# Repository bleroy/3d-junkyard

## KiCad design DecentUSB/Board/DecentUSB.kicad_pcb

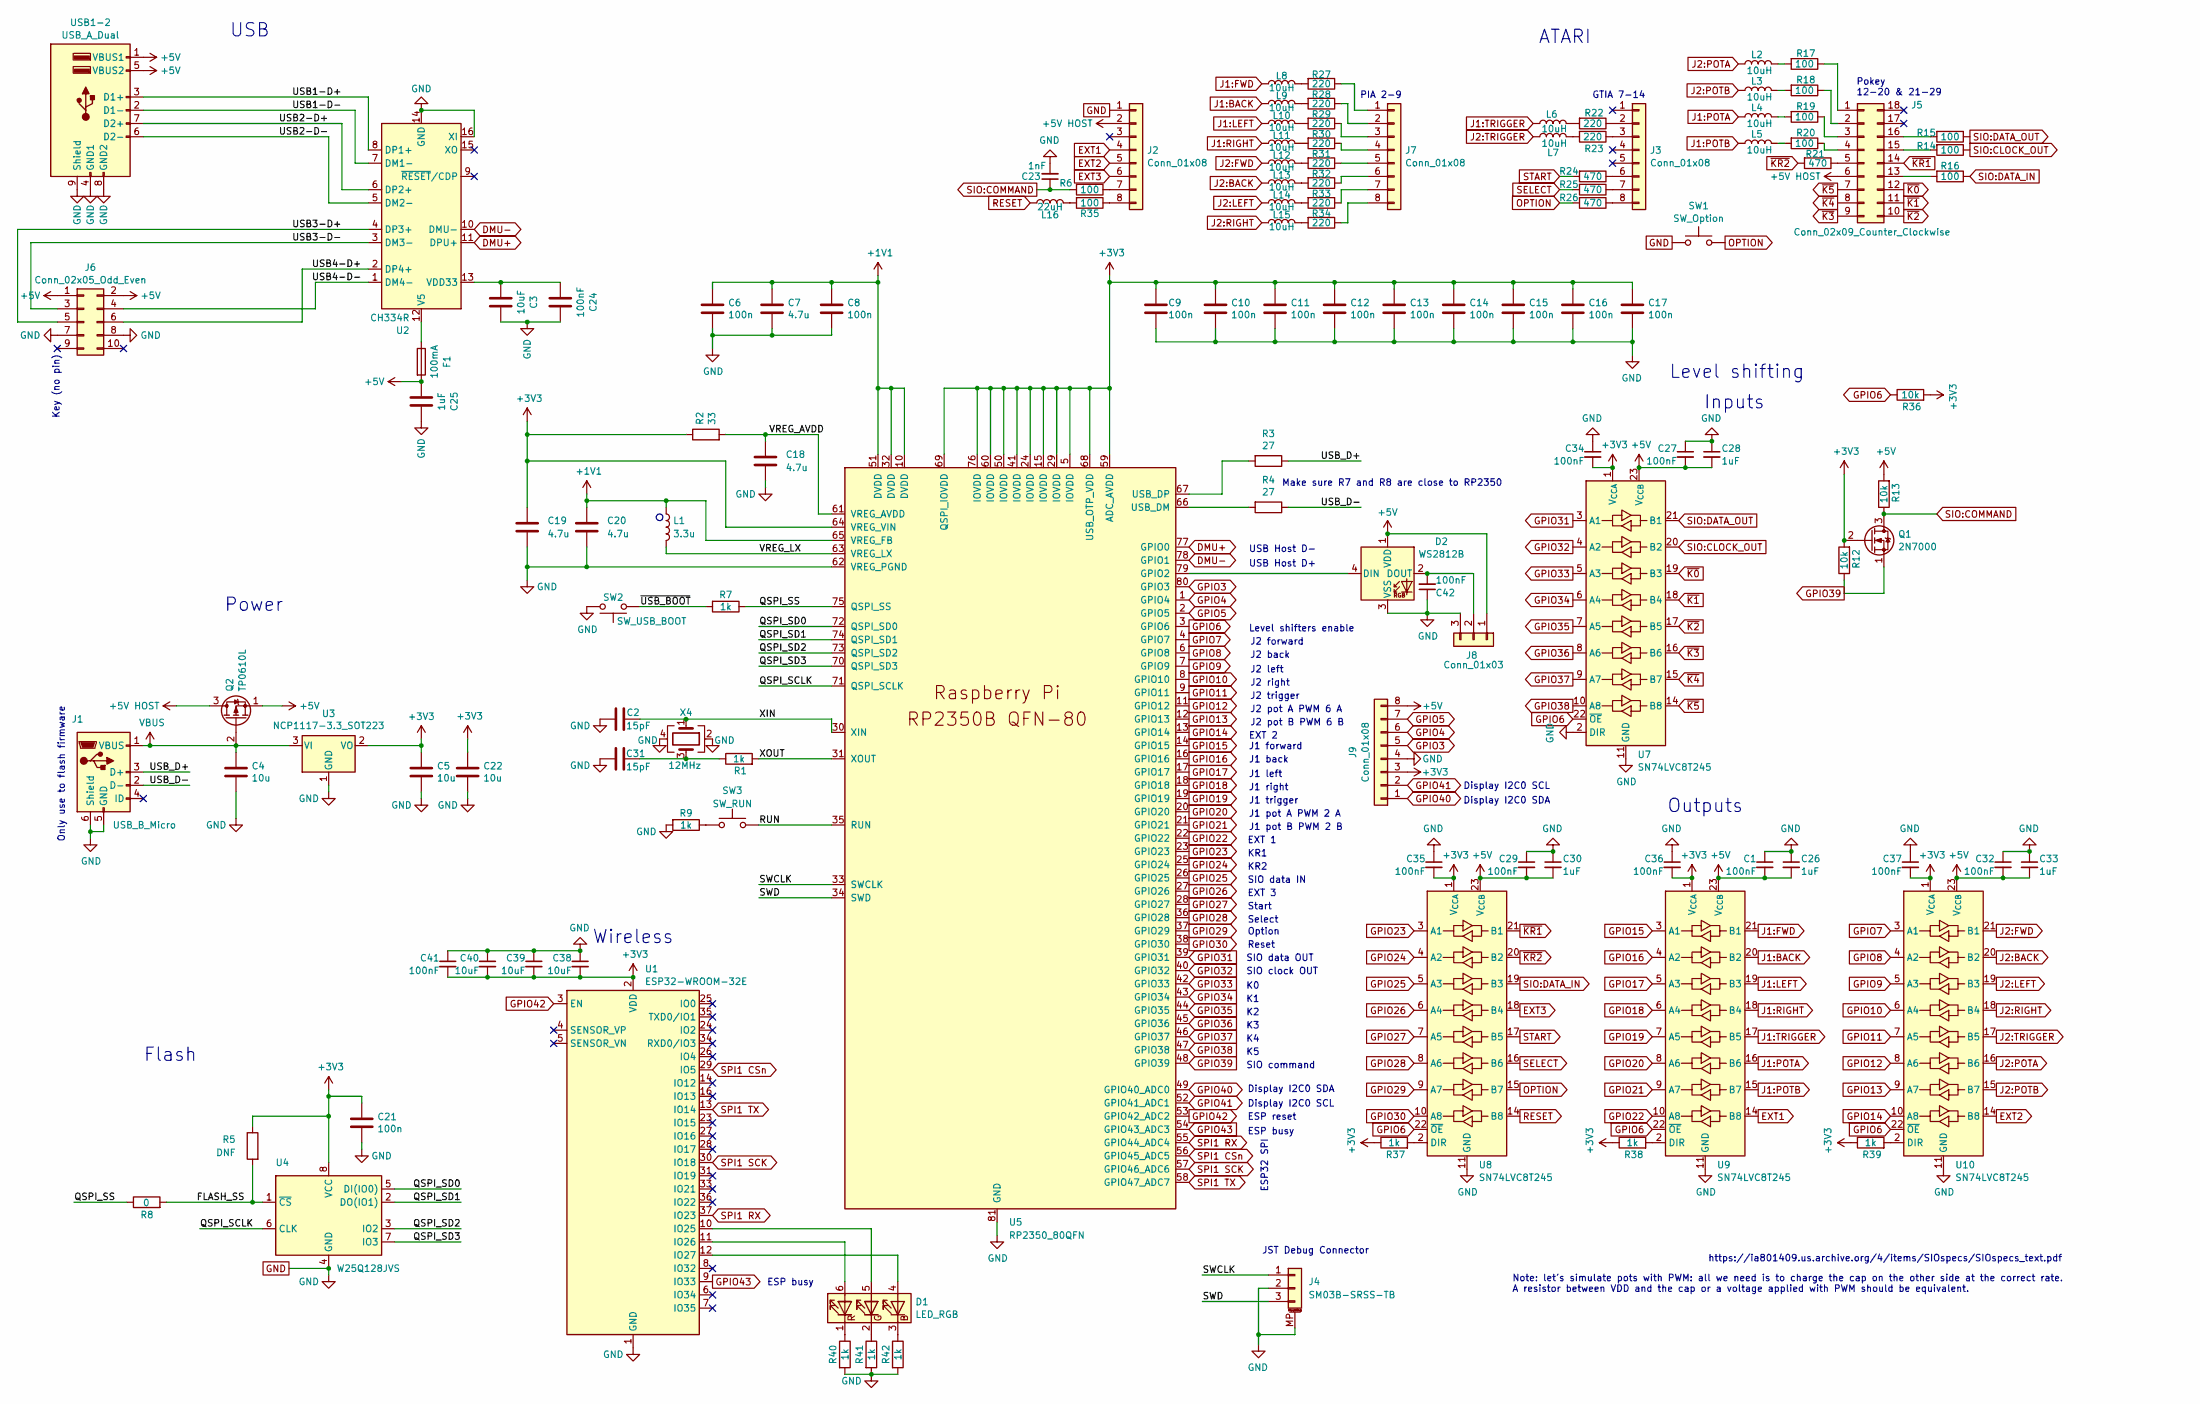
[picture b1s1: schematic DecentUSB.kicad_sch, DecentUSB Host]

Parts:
C1, C27, C29, C32, C34, C35, C36, C37, C41, C42: 100nF; C_0402_1005Metric
C2, C31: 15pF; C_0402_1005Metric
C3: 10uF; C_0402_1005Metric; JLCPCB Part # C19702
C4, C5, C22: 10u; C_0402_1005Metric
C6, C8, C9, C10, C11, C12, C13, C14, C15, C16, C17, C21: 100n; C_0402_1005Metric
C7, C18, C19, C20: 4.7u; C_0402_1005Metric
C23: 1nF; C_0402_1005Metric
C24: 100nF; C_0402_1005Metric; JLCPCB Part # C14663
C25: 1uF; C_0402_1005Metric; JLCPCB Part # C15849
C26, C28, C30, C33: 1uF; C_0402_1005Metric
C38, C39, C40: 10uF; C_0402_1005Metric
D1: LED_RGB; LED_RGB_5050-6; JLCPCB Part # C2999145
D2: WS2812B; LED_WS2812B_PLCC4_5.0x5.0mm_P3.2mm
F1: 100mA; Fuse_1206_3216Metric; JLCPCB Part # C269108
J1: USB_B_Micro; USB_Micro-B_Amphenol_10103594-0001LF_Horizontal
J2, J3, J7: Conn_01x08; PinHeader_1x08_P2.54mm_Vertical
J4: SM03B-SRSS-TB; JST_SH_SM03B-SRSS-TB_1x03-1MP_P1.00mm_Horizontal
J5: Conn_02x09_Counter_Clockwise; PinHeader_2x09_P2.54mm_Vertical
J6: Conn_02x05_Odd_Even; PinHeader_2x05_P2.54mm_Vertical
J8: Conn_01x03; JST_SH_SM03B-SRSS-TB_1x03-1MP_P1.00mm_Horizontal
J9: Conn_01x08; PinSocket_1x08_P2.54mm_Vertical
L1: 3.3u; L_0603_1608Metric
L2, L3, L4, L5, L6, L7, L8, L9, L10, L11, L12, L13, L14, L15: 10uH; L_0603_1608Metric
L16: 22uH; L_0805_2012Metric
Q1: 2N7000; SOT-23; JLCPCB Part # C22446827
Q2: TP0610L; SOT-23; JLCPCB Part # C193222
R1, R7, R9, R37, R38, R39, R40, R41, R42: 1k; R_0402_1005Metric
R2: 33; R_0402_1005Metric
R3, R4: 27; R_0402_1005Metric
R5: DNF; R_0402_1005Metric
R6, R14, R15, R16, R17, R18, R19, R20, R35: 100; R_0402_1005Metric
R8: 0; R_0402_1005Metric
R12, R13, R36: 10k; R_0402_1005Metric
R21, R24, R25, R26: 470; R_0402_1005Metric
R22, R23, R27, R28, R29, R30, R31, R32, R33, R34: 220; R_0402_1005Metric
SW1: SW_Option; SW_Push_1P1T_XKB_TS-1177A-C; JLCPCB Part # C318884
SW2: SW_USB_BOOT; SW_Push_1P1T_XKB_TS-1177A-C
SW3: SW_RUN; SW_Push_1P1T_XKB_TS-1177A-C
U1: ESP32-WROOM-32E; ESP32-WROOM-32D; JLCPCB Part # C701341
U2: CH334R; QSOP-16_3.9x4.9mm_P0.635mm; JLCPCB Part # C4154405
U3: NCP1117-3.3_SOT223; SOT-223-3_TabPin2; JLCPCB Part # C7462742
U4: W25Q128JVS; SOIC-8_7.5x5.85mm_P1.27mm; JLCPCB Part # C97521
U5: RP2350_80QFN; RP2350-QFN-80-1EP_10x10_P0.4mm_EP3.4x3.4mm_ThermalVias
U7, U8, U9, U10: SN74LVC8T245; TSSOP-24_4.4x7.8mm_P0.65mm; JLCPCB Part # C27643
USB1-2: USB_A_Dual; USB_A_CUI_UJ2-ADH-TH_Horizontal_Stacked
X4: 12MHz; Crystal_SMD_Abracon_ABM8AIG-4Pin_3.2x2.5mm; JLCPCB Part # C20625731

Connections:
+1V1: C6.1, C7.1, C8.1, C20.1, L1.1, U5.10 (DVDD), U5.32 (DVDD), U5.51 (DVDD), U5.65 (VREG_FB)
+3V3: C5.1, C9.1, C10.1, C11.1, C12.1, C13.1, C14.1, C15.1, C16.1, C17.1, C19.1, C21.1, C22.1, C34.2, C35.2, C36.2, C37.2, C38.2, C39.2, C40.2, C41.2, J9.3, Q1.2 (G), R2.1, R5.1, R12.2, R36.2, R37.1, R38.1, R39.1, U1.2 (VDD), U3.2 (VO), U4.8 (VCC), U5.5 (IOVDD), U5.15 (IOVDD), U5.24 (IOVDD), U5.29 (IOVDD), U5.41 (IOVDD), U5.50 (IOVDD), U5.59 (ADC_AVDD), U5.60 (IOVDD), U5.64 (VREG_VIN), U5.68 (USB_OTP_VDD), U5.69 (QSPI_IOVDD), U5.76 (IOVDD), U7.1 (V_{CCA}), U8.1 (V_{CCA}), U9.1 (V_{CCA}), U10.1 (V_{CCA})
+5V: C1.2, C25.1, C26.2, C27.2, C28.2, C29.2, C30.2, C32.2, C33.2, D2.1 (VDD), F1.2, J6.1, J6.2, J8.1, J9.8, Q2.1 (S), R13.2, U7.23 (V_{CCB}), U7.24 (V_{CCB}), U8.23 (V_{CCB}), U8.24 (V_{CCB}), U9.23 (V_{CCB}), U9.24 (V_{CCB}), U10.23 (V_{CCB}), U10.24 (V_{CCB}), USB1-2.1 (VBUS1), USB1-2.5 (VBUS2)
+5V HOST: J2.2, J5.6, Q2.3 (D)
/FLASH_SS: R5.2, R8.2, U4.1 (~CS)
/QSPI_SCLK: U4.6 (CLK), U5.71 (QSPI_SCLK)
/QSPI_SD0: U4.5 (DI(IO0)), U5.72 (QSPI_SD0)
/QSPI_SD1: U4.2 (DO(IO1)), U5.74 (QSPI_SD1)
/QSPI_SD2: U4.3 (IO2), U5.73 (QSPI_SD2)
/QSPI_SD3: U4.7 (IO3), U5.70 (QSPI_SD3)
/QSPI_SS: R7.1, R8.1, U5.75 (QSPI_SS)
/RUN: SW3.2, U5.35 (RUN)
/SWCLK: J4.1, U5.33 (SWCLK)
/SWD: J4.3, U5.34 (SWD)
/USB1-D+: U2.8 (DP1+), USB1-2.3 (D1+)
/USB1-D-: U2.7 (DM1-), USB1-2.2 (D1-)
/USB2-D+: U2.6 (DP2+), USB1-2.7 (D2+)
/USB2-D-: U2.5 (DM2-), USB1-2.6 (D2-)
/USB3-D+: J6.5, U2.4 (DP3+)
/USB3-D-: J6.3, U2.3 (DM3-)
/USB4-D+: J6.6, U2.2 (DP4+)
/USB4-D-: J6.4, U2.1 (DM4-)
/USB_D+: J1.3 (D+), R3.1
/USB_D-: J1.2 (D-), R4.1
/VREG_AVDD: C18.1, R2.2, U5.61 (VREG_AVDD)
/VREG_LX: L1.2, U5.63 (VREG_LX)
/XIN: C2.1, U5.30 (XIN), X4.1
/XOUT: R1.2, U5.31 (XOUT)
/~USB_BOOT: R7.2, SW2.1
DMU+: U2.11 (DPU+), U5.77 (GPIO0)
DMU-: U2.10 (DMU-), U5.78 (GPIO1)
EXT1: J2.4, U9.14 (B8)
EXT2: J2.5, U10.14 (B8)
EXT3: J2.6, U8.18 (B4)
GND: C1.1, C2.2, C3.2, C4.2, C5.2, C6.2, C7.2, C8.2, C9.2, C10.2, C11.2, C12.2, C13.2, C14.2, C15.2, C16.2, C17.2, C18.2, C19.2, C20.2, C21.2, C22.2, C23.2, C24.2, C25.2, C26.1, C27.1, C28.1, C29.1, C30.1, C31.1, C32.1, C33.1, C34.1, C35.1, C36.1, C37.1, C38.1, C39.1, C40.1, C41.1, C42.1, D2.3 (VSS), J1.5 (GND), J1.6 (Shield), J2.1, J4.2, J4.MP (MountPin), J6.7, J6.8, J8.3, J8.MP, J9.4, R9.2, R40.2, R41.2, R42.2, SW1.1, SW2.2, U1.1 (GND), U1.15 (GND), U1.38 (GND), U1.39 (GND), U2.14 (GND), U2.16 (XI), U3.1 (GND), U4.4 (GND), U5.62 (VREG_PGND), U5.81 (GND), U7.2 (DIR), U7.11 (GND), U7.12 (GND), U7.13 (GND), U8.11 (GND), U8.12 (GND), U8.13 (GND), U9.11 (GND), U9.12 (GND), U9.13 (GND), U10.11 (GND), U10.12 (GND), U10.13 (GND), USB1-2.4 (GND1), USB1-2.8 (GND2), USB1-2.9 (Shield), X4.2, X4.4
GPIO3: J9.5, U5.80 (GPIO3)
GPIO4: J9.6, U5.1 (GPIO4)
GPIO5: J9.7, U5.2 (GPIO5)
GPIO6: R36.1, U5.3 (GPIO6), U7.22 (~OE), U8.22 (~OE), U9.22 (~OE), U10.22 (~OE)
GPIO7: U5.4 (GPIO7), U10.3 (A1)
GPIO8: U5.6 (GPIO8), U10.4 (A2)
GPIO9: U5.7 (GPIO9), U10.5 (A3)
GPIO10: U5.8 (GPIO10), U10.6 (A4)
GPIO11: U5.9 (GPIO11), U10.7 (A5)
GPIO12: U5.11 (GPIO12), U10.8 (A6)
GPIO13: U5.12 (GPIO13), U10.9 (A7)
GPIO14: U5.13 (GPIO14), U10.10 (A8)
GPIO15: U5.14 (GPIO15), U9.3 (A1)
GPIO16: U5.16 (GPIO16), U9.4 (A2)
GPIO17: U5.17 (GPIO17), U9.5 (A3)
GPIO18: U5.18 (GPIO18), U9.6 (A4)
GPIO19: U5.19 (GPIO19), U9.7 (A5)
GPIO20: U5.20 (GPIO20), U9.8 (A6)
GPIO21: U5.21 (GPIO21), U9.9 (A7)
GPIO22: U5.22 (GPIO22), U9.10 (A8)
GPIO23: U5.23 (GPIO23), U8.3 (A1)
GPIO24: U5.25 (GPIO24), U8.4 (A2)
GPIO25: U5.26 (GPIO25), U8.5 (A3)
GPIO26: U5.27 (GPIO26), U8.6 (A4)
GPIO27: U5.28 (GPIO27), U8.7 (A5)
GPIO28: U5.36 (GPIO28), U8.8 (A6)
GPIO29: U5.37 (GPIO29), U8.9 (A7)
GPIO30: U5.38 (GPIO30), U8.10 (A8)
GPIO31: U5.39 (GPIO31), U7.3 (A1)
GPIO32: U5.40 (GPIO32), U7.4 (A2)
GPIO33: U5.42 (GPIO33), U7.5 (A3)
GPIO34: U5.43 (GPIO34), U7.6 (A4)
GPIO35: U5.44 (GPIO35), U7.7 (A5)
GPIO36: U5.45 (GPIO36), U7.8 (A6)
GPIO37: U5.46 (GPIO37), U7.9 (A7)
GPIO38: U5.47 (GPIO38), U7.10 (A8)
GPIO39: Q1.1 (S), R12.1, U5.48 (GPIO39)
GPIO40: J9.1, U5.49 (GPIO40_ADC0)
GPIO41: J9.2, U5.52 (GPIO41_ADC1)
GPIO42: U1.3 (EN), U5.53 (GPIO42_ADC2)
GPIO43: U1.9 (IO33), U5.54 (GPIO43_ADC3)
J1:BACK: L9.1, U9.20 (B2)
J1:FWD: L8.1, U9.21 (B1)
J1:LEFT: L10.1, U9.19 (B3)
J1:POTA: L4.1, U9.16 (B6)
J1:POTB: L5.1, U9.15 (B7)
J1:RIGHT: L11.1, U9.18 (B4)
J1:TRIGGER: L6.1, U9.17 (B5)
J2:BACK: L13.1, U10.20 (B2)
J2:FWD: L12.1, U10.21 (B1)
J2:LEFT: L14.1, U10.19 (B3)
J2:POTA: L2.1, U10.16 (B6)
J2:POTB: L3.1, U10.15 (B7)
J2:RIGHT: L15.1, U10.18 (B4)
J2:TRIGGER: L7.1, U10.17 (B5)
unnamed: C31.2, R1.1, X4.3
unnamed: D1.4 (BA), U1.12 (IO27)
unnamed: D1.3 (BK), R42.1
unnamed: D1.5 (GA), U1.10 (IO25)
unnamed: D1.2 (GK), R41.1
unnamed: D1.6 (RA), U1.11 (IO26)
unnamed: D1.1 (RK), R40.1
unnamed: D2.4 (DIN), U5.79 (GPIO2)
unnamed: C42.2, D2.2 (DOUT), J8.2
unnamed: J2.7, R6.1
unnamed: J2.8, R35.1
unnamed: J3.2, R22.1
unnamed: J3.3, R23.1
unnamed: J3.6, R24.1
unnamed: J3.7, R25.1
unnamed: J3.8, R26.1
unnamed: J5.1, R17.1
unnamed: J5.2, R18.1
unnamed: J5.3, R19.1
unnamed: J5.4, R20.1
unnamed: J5.5, R21.1
unnamed: J5.13, R16.2
unnamed: J5.15, R14.2
unnamed: J5.16, R15.2
unnamed: J7.1, R27.1
unnamed: J7.2, R28.1
unnamed: J7.3, R29.1
unnamed: J7.4, R30.1
unnamed: J7.5, R31.1
unnamed: J7.6, R32.1
unnamed: J7.7, R33.1
unnamed: J7.8, R34.1
unnamed: L2.2, R17.2
unnamed: L3.2, R18.2
unnamed: L4.2, R19.2
unnamed: L5.2, R20.2
unnamed: L6.2, R22.2
unnamed: L7.2, R23.2
unnamed: L8.2, R27.2
unnamed: L9.2, R28.2
unnamed: L10.2, R29.2
unnamed: L11.2, R30.2
unnamed: L12.2, R31.2
unnamed: L13.2, R32.2
unnamed: L14.2, R33.2
unnamed: L15.2, R34.2
unnamed: L16.2, R35.2
unnamed: R9.1, SW3.1
unnamed: F1.1, U2.12 (V5)
unnamed: C3.1, C24.1, U2.13 (VDD33)
unnamed: R4.2, U5.66 (USB_DM)
unnamed: R3.2, U5.67 (USB_DP)
unnamed: R37.2, U8.2 (DIR)
unnamed: R38.2, U9.2 (DIR)
unnamed: R39.2, U10.2 (DIR)
OPTION: R26.2, SW1.2, U8.15 (B7)
RESET: L16.1, U8.14 (B8)
SELECT: R25.2, U8.16 (B6)
SIO:CLOCK_OUT: R14.1, U7.20 (B2)
SIO:COMMAND: C23.1, Q1.3 (D), R6.2, R13.1
SIO:DATA_IN: R16.1, U8.19 (B3)
SIO:DATA_OUT: R15.1, U7.21 (B1)
SPI1 CSn: U1.29 (IO5), U5.56 (GPIO45_ADC5)
SPI1 RX: U1.37 (IO23), U5.55 (GPIO44_ADC4)
SPI1 SCK: U1.30 (IO18), U5.57 (GPIO46_ADC6)
SPI1 TX: U1.13 (IO14), U5.58 (GPIO47_ADC7)
START: R24.2, U8.17 (B5)
VBUS: C4.1, J1.1 (VBUS), Q2.2 (G), U3.3 (VI)
~K0: J5.12, U7.19 (B3)
~K1: J5.11, U7.18 (B4)
~K2: J5.10, U7.17 (B5)
~K3: J5.9, U7.16 (B6)
~K4: J5.8, U7.15 (B7)
~K5: J5.7, U7.14 (B8)
~KR1: J5.14, U8.21 (B1)
~KR2: R21.2, U8.20 (B2)

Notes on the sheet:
Level shifting
J2 trigger
Display I2C0 SDA
J1 right
ESP reset
KR2
ATARI
GTIA 7-14
USB Host D-
SIO command
J2 left
Display I2C0 SCL
Note: let's simulate pots with PWM: all we need is to charge the cap on the other side at the correct rate. A resistor between VDD and the cap or a voltage applied with PWM should be equivalent.
PIA 2-9
ESP32 SPI
SIO clock OUT
Power
J2 pot B PWM 6 B
Option
Start
KR1
J1 pot A PWM 2 A
J2 forward
J1 pot B PWM 2 B
Select
J2 back
Wireless
Reset
https://ia801409.us.archive.org/4/items/SIOspecs/SIOspecs_text.pdf
Only use to flash firmware
J1 back
EXT 1
ESP busy
Make sure R7 and R8 are close to RP2350
J2 pot A PWM 6 A
J2 right
Outputs
Inputs
EXT 2
SIO data OUT

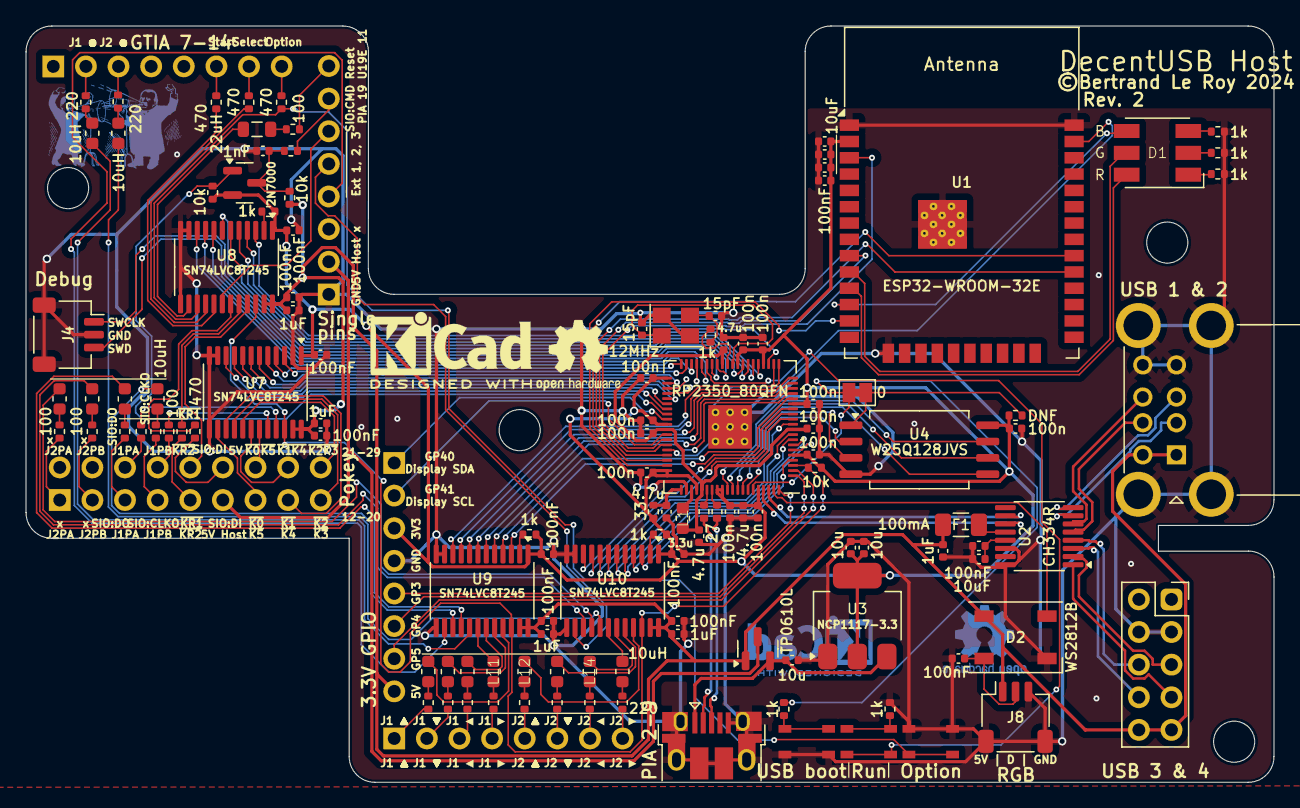
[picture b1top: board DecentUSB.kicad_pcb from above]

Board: 2 copper layers, 97.2 x 58.9 mm, 126 parts (0 on the bottom side), 166 nets.

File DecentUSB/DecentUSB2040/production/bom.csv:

Designator,Footprint,Quantity,Value,LCSC Part #
"C1, C10, C11, C12, C13, C14, C15, C19, C24, C27, C29, C32, C34, C35, C36, C37, C41, C42, C6, C8, C9",0402,21,100nF,C1525
"C16, C20, C25, C26, C28, C30, C33, C7",0402,8,1uF,C52923
"C17, C18",0402,2,15pF,C1548
"C2, C3, C38, C39, C4, C40, C5",0402,7,10uF,C15525
C23,0402,1,1nF,C1523
D1,Nexperia_CFP3_SOD-123W,1,MBR120VLSFT1G,C223608
D2,WS2812C,1,WS2812B,C4154872
F1,1206,1,100mA,C269108
J1,USB_Micro-B,1,USB_B_Micro,C2765187
J10,JST_SH_BM03B-SRSS-TB_1x03-1MP_P1.00mm_Vertical,1,SM03B-SRSS-TB,C160389
J8,JST_SH_BM03B-SRSS-TB_1x03-1MP_P1.00mm_Vertical,1,Conn_01x03,C160389
"L10, L11, L12, L13, L14, L15, L2, L3, L4, L5, L6, L7, L8, L9",0603,14,10uH,C1035
L16,0805,1,22uH,C105501
Q1,SOT-23,1,2N7000,C22446827
Q2,SOT-23,1,DMG2305UX,C150470
"R1, R37, R38, R39, R40, R7, R8",0402,7,1k,C11702
"R11, R12, R13, R36",0402,4,10k,C25744
"R14, R15, R16, R17, R18, R19, R20, R35, R6",0402,9,100,C25076
"R2, R3, R4, R5",0805,4,27,C17561
"R21, R24, R25, R26",0402,4,470,C25117
"R22, R23, R27, R28, R29, R30, R31, R32, R33, R34",0402,10,220,C25091
"SW1, SW2, SW3, SW4",Tactile_Switch_Basic_XKB_TS-1187A,4,SW_TACTILE,C318884
U1,ESP32-WROOM-32D,1,ESP32-WROOM-32E,C701341
"U10, U7, U8, U9",TSSOP-24_4.4x7.8mm_P0.65mm,4,SN74LVC8T245,C27643
U2,QSOP-16_3.9x4.9mm_P0.635mm,1,CH334R,C4154405
U3,SOT-223-3_TabPin2,1,NCP1117-3.3,C6186
U4,QFN-56-1EP_7x7mm_P0.4mm_EP3.2x3.2mm,1,RP2040,C2040
U5,SOIC-8_5.23x5.23mm_P1.27mm,1,W25Q128JVS,C97521
X1,Crystal_SMD_Abracon_ABM8AIG-4Pin_3.2x2.5mm,1,12MHz,C9002

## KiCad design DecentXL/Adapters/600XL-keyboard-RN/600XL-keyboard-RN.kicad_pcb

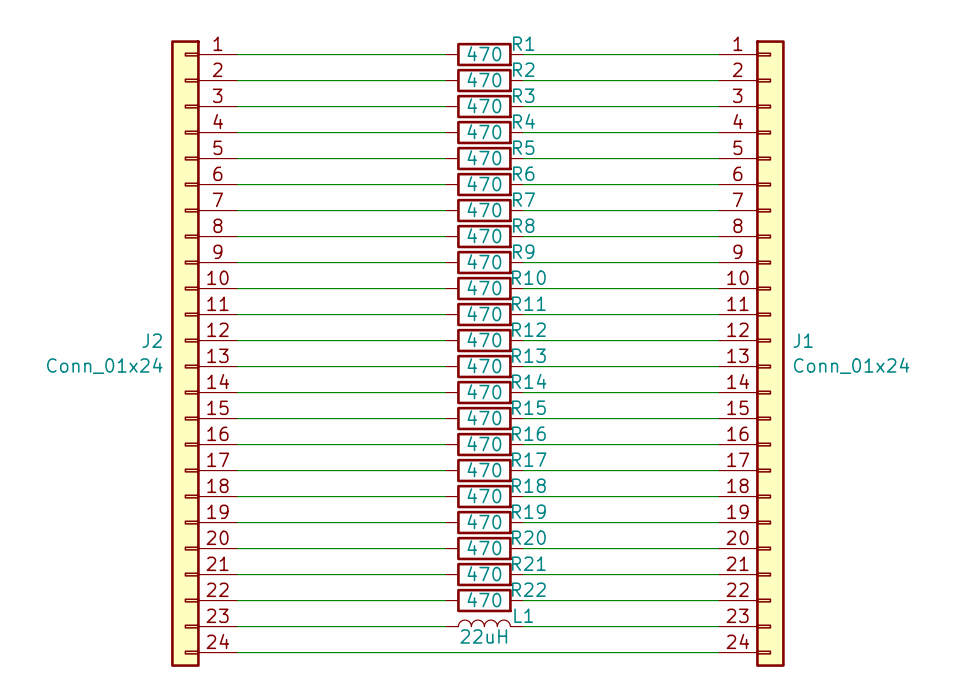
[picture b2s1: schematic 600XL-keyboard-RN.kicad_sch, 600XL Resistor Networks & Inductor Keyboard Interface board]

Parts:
J1, J2: Conn_01x24; PinHeader_1x24_P2.54mm_Vertical
L1: 22uH; L_0603_1608Metric; JLCPCB Part # C361669
R1, R2, R3, R4, R5, R6, R7, R8, R9, R10, R11, R12, R13, R14, R15, R16, R17, R18, R19, R20, R21, R22: 470; R_0603_1608Metric; JLCPCB Part # C23179

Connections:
unnamed: J1.1, R1.2
unnamed: J1.2, R2.2
unnamed: J1.3, R3.2
unnamed: J1.4, R4.2
unnamed: J1.5, R5.2
unnamed: J1.6, R6.2
unnamed: J1.7, R7.2
unnamed: J1.8, R8.2
unnamed: J1.9, R9.2
unnamed: J1.10, R10.2
unnamed: J1.11, R11.2
unnamed: J1.12, R12.2
unnamed: J1.13, R13.2
unnamed: J1.14, R14.2
unnamed: J1.15, R15.2
unnamed: J1.16, R16.2
unnamed: J1.17, R17.2
unnamed: J1.18, J2.18, R18.1, R18.2
unnamed: J1.19, J2.19, R19.1, R19.2
unnamed: J1.20, R20.2
unnamed: J1.21, R21.2
unnamed: J1.22, R22.2
unnamed: J1.23, L1.2
unnamed: J1.24, J2.24
unnamed: J2.1, R1.1
unnamed: J2.2, R2.1
unnamed: J2.3, R3.1
unnamed: J2.4, R4.1
unnamed: J2.5, R5.1
unnamed: J2.6, R6.1
unnamed: J2.7, R7.1
unnamed: J2.8, R8.1
unnamed: J2.9, R9.1
unnamed: J2.10, R10.1
unnamed: J2.11, R11.1
unnamed: J2.12, R12.1
unnamed: J2.13, R13.1
unnamed: J2.14, R14.1
unnamed: J2.15, R15.1
unnamed: J2.16, R16.1
unnamed: J2.17, R17.1
unnamed: J2.20, R20.1
unnamed: J2.21, R21.1
unnamed: J2.22, R22.1
unnamed: J2.23, L1.1

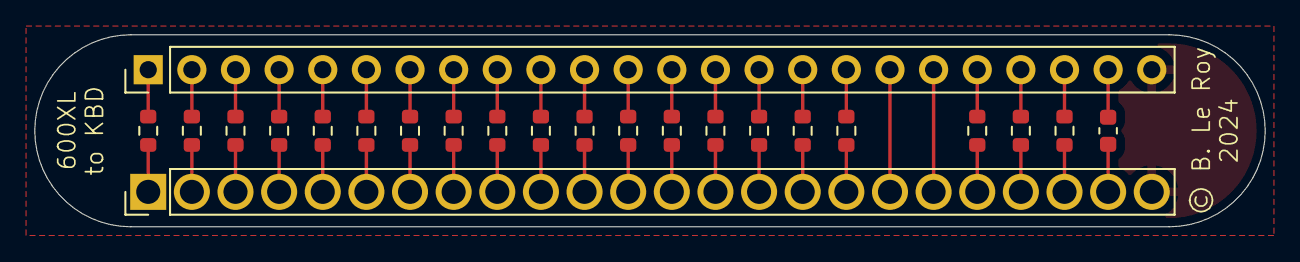
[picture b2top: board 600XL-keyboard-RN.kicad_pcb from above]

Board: 2 copper layers, 71.6 x 11.2 mm, 23 parts (0 on the bottom side), 45 nets.

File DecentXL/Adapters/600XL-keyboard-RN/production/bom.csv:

Designator,Footprint,Quantity,Value,LCSC Part #
L1,0603,1,22uH,C361669
"R1, R10, R11, R12, R13, R14, R15, R16, R17, R18, R19, R2, R20, R21, R22, R3, R4, R5, R6, R7, R8, R9",0603,22,470,C23179

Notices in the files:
DecentUSB/Board/DecentUSB.kicad_pcb:
© Bertrand Le Roy 2024
DecentXL/Adapters/600XL-keyboard-RN/600XL-keyboard-RN.kicad_pcb:
© B. Le Roy
